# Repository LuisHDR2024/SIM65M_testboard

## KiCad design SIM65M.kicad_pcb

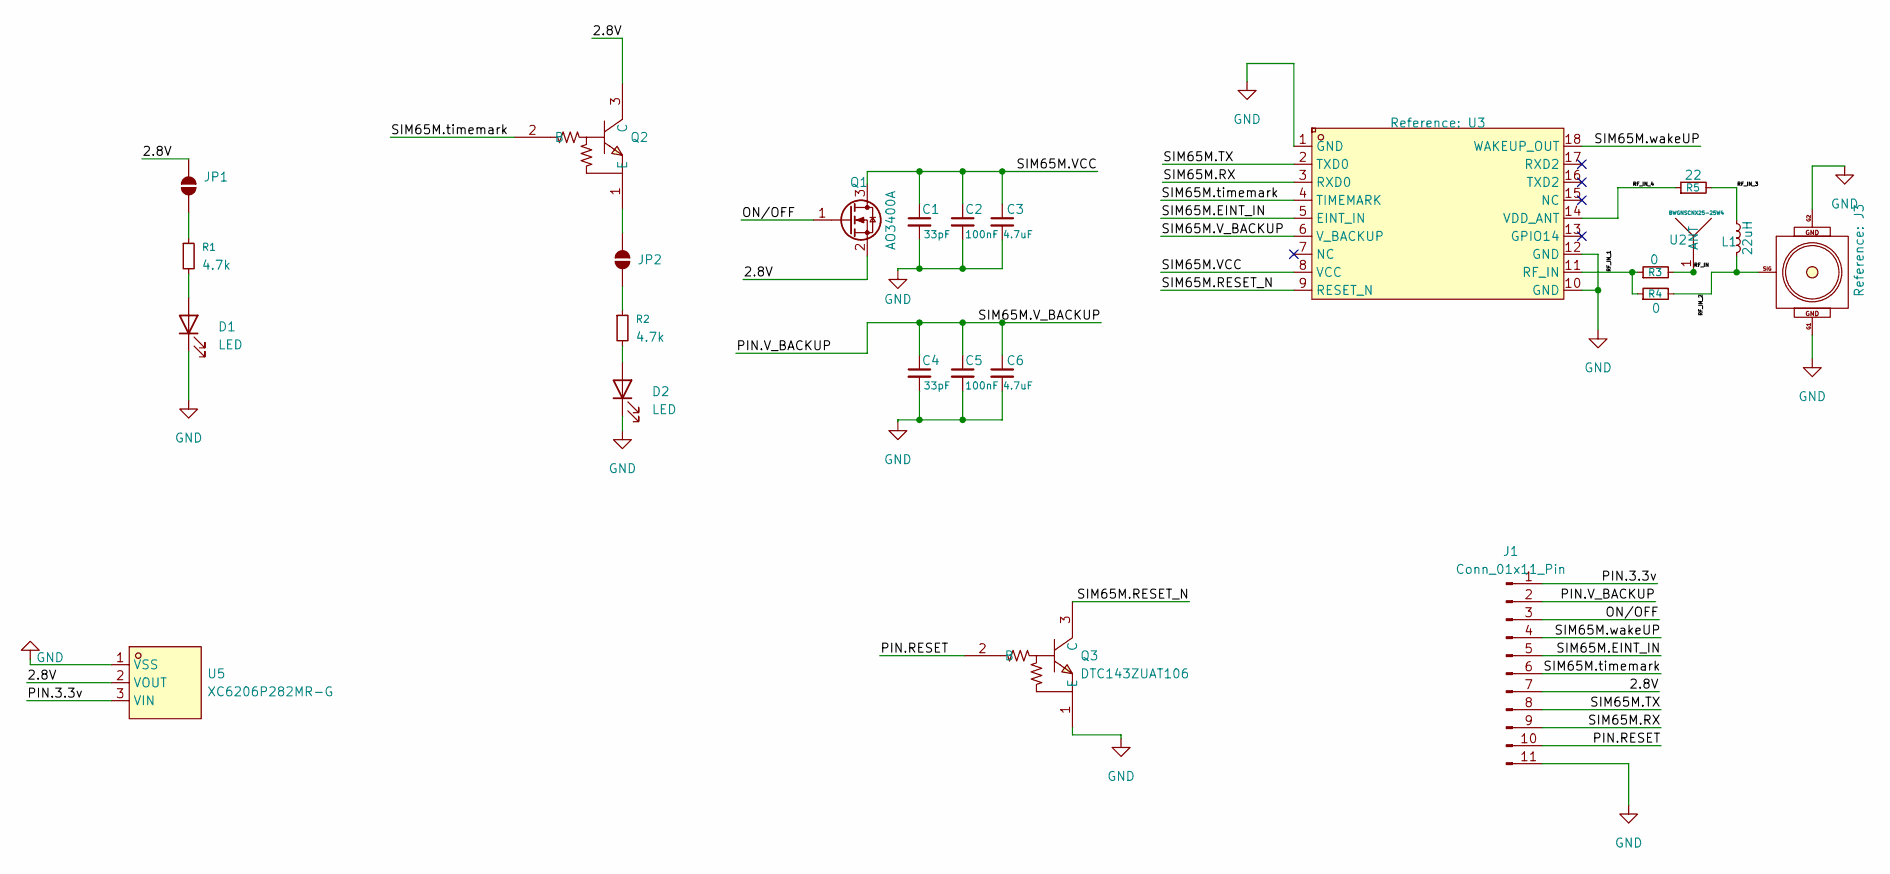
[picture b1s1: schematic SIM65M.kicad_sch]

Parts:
C1, C4: 33pF; C_0603_1608Metric
C2, C5: 100nF; C_0603_1608Metric
C3, C6: 4.7uF; C_0603_1608Metric
D1, D2: LED; LED_0603_1608Metric
J1: Conn_01x11_Pin; PinHeader_1x11_P2.54mm_Vertical
J3: U.FL-R-SMT_10_; U.FL-R-SMT_10_-foot; PARTREV 11.11.15
JP1, JP2: SolderJumper_2_Open; SolderJumper-2_P1.3mm_Open_TrianglePad1.0x1.5mm
L1: 22uH; L_0402_1005Metric
Q1: AO3400A; SOT-23
Q2, Q3: DTC143ZUAT106; SC-70-3_L2.1-W1.3-P1.30-LS2.1-TR; MPN DTC143ZUAT106; LCSC Part C190246
R1, R2: 4.7k; R_0603_1608Metric
R3, R4: 0; R_0201_0603Metric_Pad0.64x0.40mm_HandSolder
R5: 22; R_0201_0603Metric_Pad0.64x0.40mm_HandSolder
U2: BWGNSCNX25-25W4; ANT-TH_L25.0-W25.0; MPN BWGNSCNX25-25W4; LCSC Part C784398
U3: SIM65M_C7495025; SIM65M_foot; LCSC Part C7495025
U5: XC6206P282MR-G; SOT-23-3_L2.9-W1.6-P1.90-LS2.8-BR; MPN XC6206P282MR-G; LCSC Part C2891263

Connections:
/2.8V: J1.7, JP1.2 (B), Q1.2 (S), Q2.3 (C), U5.2 (VOUT)
/ON/OFF: J1.3, Q1.1 (G)
/PIN.3.3v: J1.1, U5.3 (VIN)
/PIN.RESET: J1.10, Q3.2 (B)
/PIN.V_BACKUP: C4.1, C5.1, C6.1, J1.2, U3.6 (V_BACKUP)
/RF_IN: R3.2, U2.1 (ANT_1)
/RF_IN_1: R3.1, R4.1, U3.11 (RF_IN)
/RF_IN_2: J3.SIG, L1.2, R4.2
/RF_IN_3: L1.1, R5.2
/RF_IN_4: R5.1, U3.14 (VDD_ANT)
/SIM65M.EINT_IN: J1.5, U3.5 (EINT_IN)
/SIM65M.RESET_N: Q3.3 (C), U3.9 (RESET_N)
/SIM65M.RX: J1.9, U3.3 (RXD0)
/SIM65M.TX: J1.8, U3.2 (TXD0)
/SIM65M.VCC: C1.1, C2.1, C3.1, Q1.3 (D), U3.8 (VCC)
/SIM65M.timemark: J1.6, Q2.2 (B), U3.4 (TIMEMARK)
/SIM65M.wakeUP: J1.4, U3.18 (WAKEUP_OUT)
GND: C1.2, C2.2, C3.2, C4.2, C5.2, C6.2, D1.1 (K), D2.1 (K), J1.11, J3.G1, J3.G2, Q3.1 (E), U3.1 (GND), U3.10 (GND), U3.12 (GND), U5.1 (VSS)
unnamed: D1.2 (A), R1.2
unnamed: D2.2 (A), R2.2
unnamed: JP1.1 (A), R1.1
unnamed: JP2.1 (A), Q2.1 (E)
unnamed: JP2.2 (B), R2.1

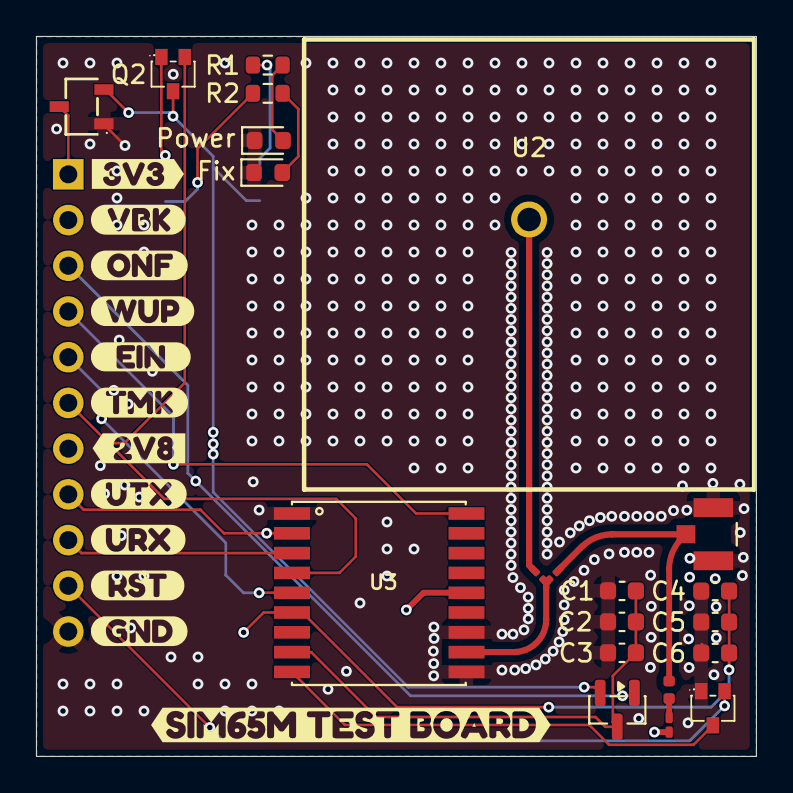
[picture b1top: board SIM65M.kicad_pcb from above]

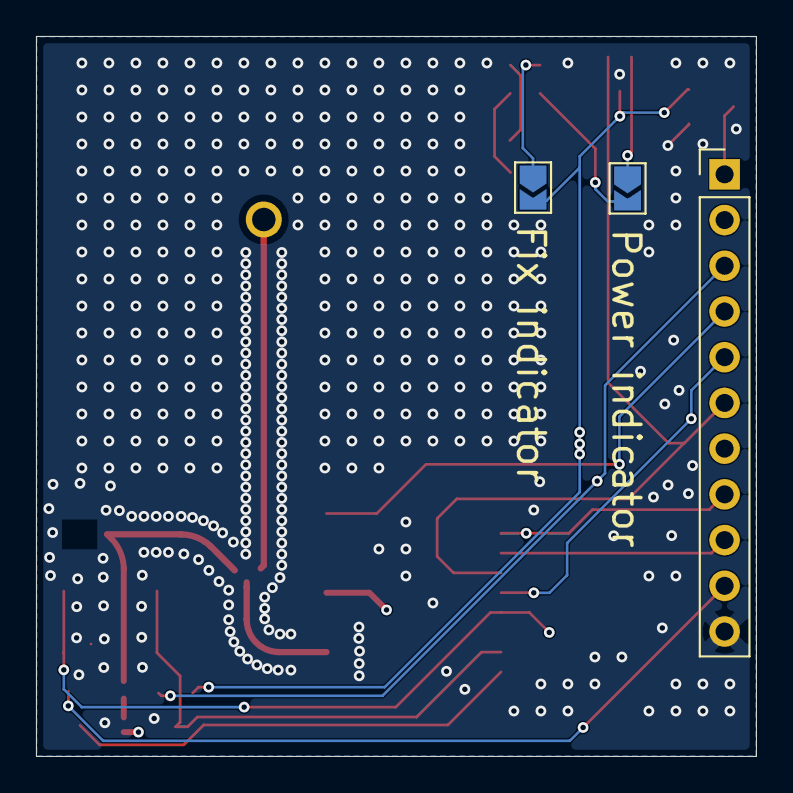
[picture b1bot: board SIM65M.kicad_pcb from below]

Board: 4 copper layers, 40.0 x 40.0 mm, 36 parts (3 on the bottom side), 23 nets.

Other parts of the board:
kibuzzard-6A279BE5: G***; kibuzzard-6A279BE5
kibuzzard-6A7951F5: G***; kibuzzard-6A7951F5
kibuzzard-6A7952C3: G***; kibuzzard-6A7952C3
kibuzzard-6A79521E: G***; kibuzzard-6A79521E
kibuzzard-6A79523C: G***; kibuzzard-6A79523C
kibuzzard-6A79525C: G***; kibuzzard-6A79525C
kibuzzard-6A795201: G***; kibuzzard-6A795201
kibuzzard-6A795219: G***; kibuzzard-6A795219
kibuzzard-6A795229: G***; kibuzzard-6A795229
kibuzzard-6A795244: G***; kibuzzard-6A795244
kibuzzard-6A795279: G***; kibuzzard-6A795279
kibuzzard-6A795305: G***; kibuzzard-6A795305

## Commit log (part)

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2026-06-21 primer guardado
2026-06-21 mini cambio
2026-06-27 agregado UFL
2026-06-29 rediseño etapa RF, agregada bifurcacion para activa/pasiva, mejoras generales en RF
2026-06-29 por si acaso
